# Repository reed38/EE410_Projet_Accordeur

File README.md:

# EE410_Projet_Accordeur

Réalisation d'un accordeur.
Utilisation d'une carte arduino pour l'échantillonage et le traitement des données, réalisation d'un pcb deux couches pour l'intégration du microphone.
2023_2024 S1
Project EE410

### authors:
Maxime Daniau,

Regnault Edgar

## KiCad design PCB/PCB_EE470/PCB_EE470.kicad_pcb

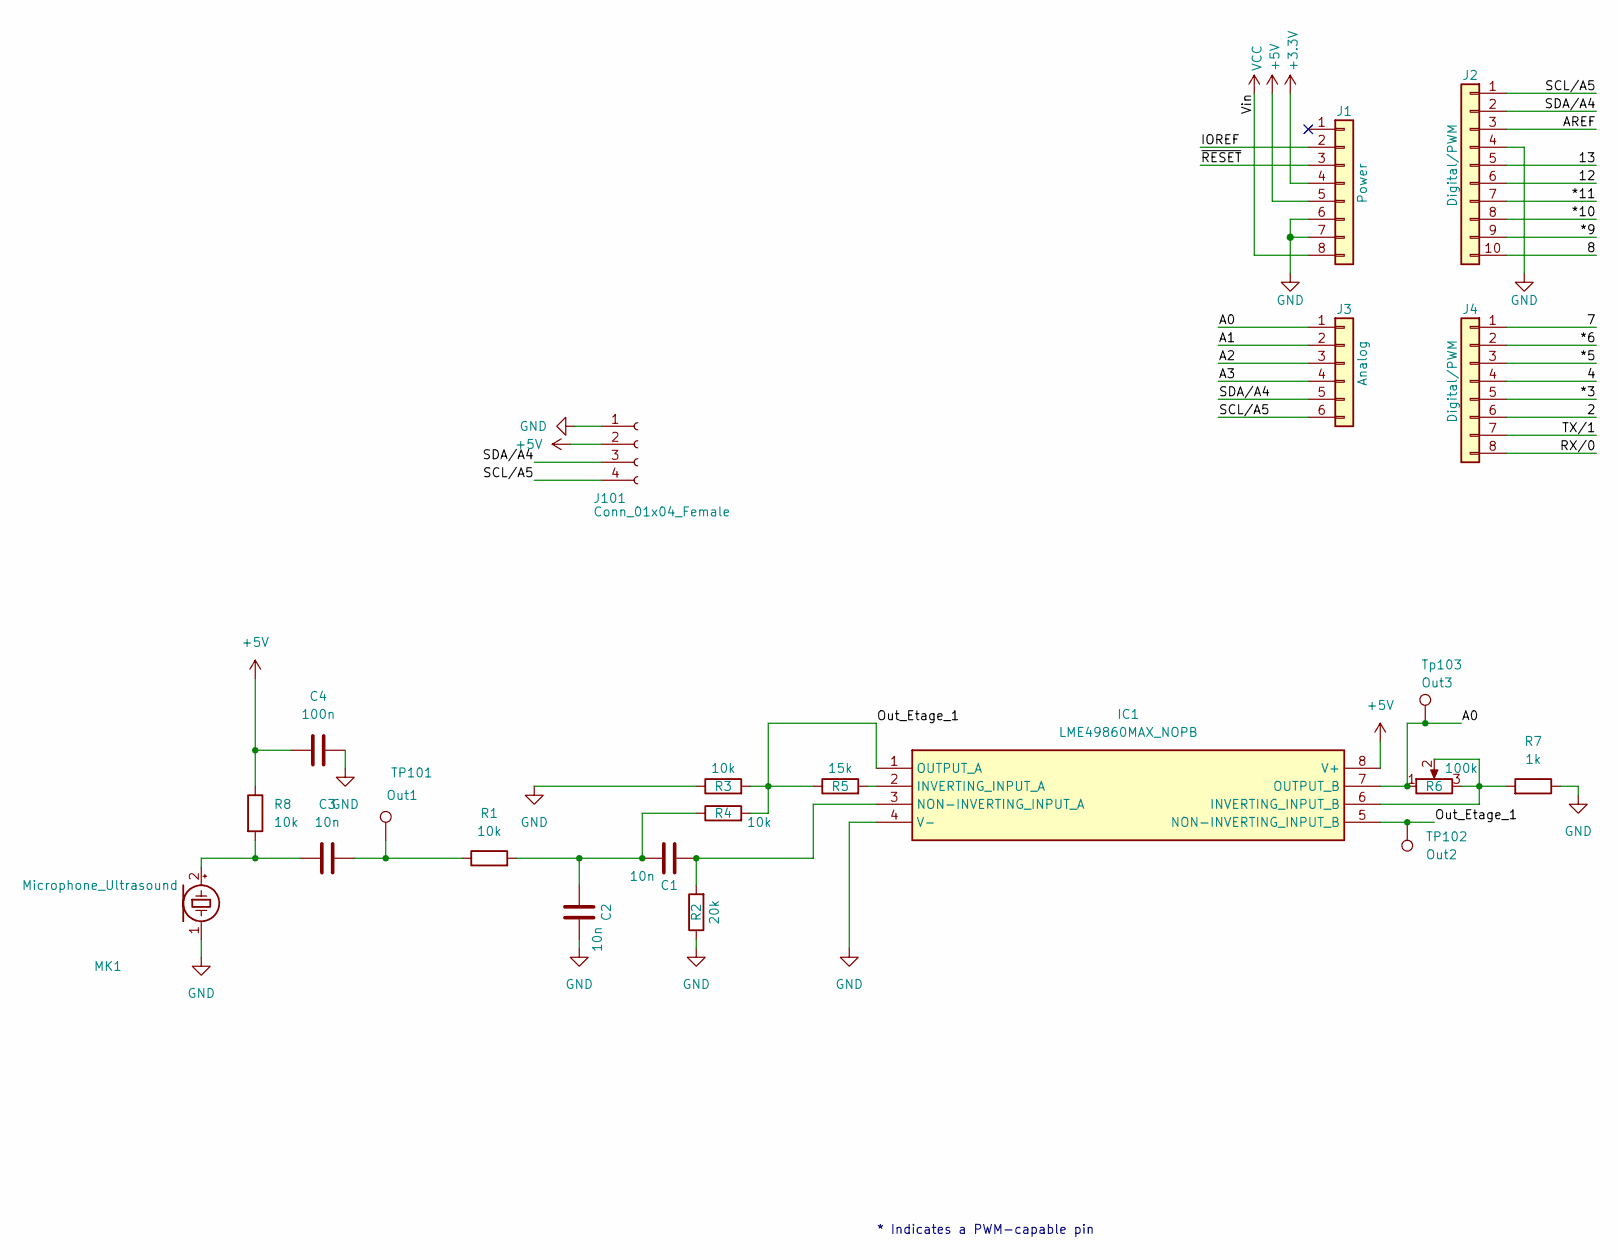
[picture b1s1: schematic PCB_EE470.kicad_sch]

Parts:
C1, C2, C3: 10n; C_1206_3216Metric_Pad1.33x1.80mm_HandSolder
C4: 100n; C_1206_3216Metric_Pad1.33x1.80mm_HandSolder
IC1: LME49860MAX_NOPB; SOIC127P600X175-8N; Mouser Part Number 926-LME49860MAX/NOPB
J1: Power; PinSocket_1x08_P2.54mm_Vertical
J2: Digital/PWM; PinSocket_1x10_P2.54mm_Vertical
J3: Analog; PinSocket_1x06_P2.54mm_Vertical
J4: Digital/PWM; PinSocket_1x08_P2.54mm_Vertical
J101: Conn_01x04_Female; JST_XH_B4B-XH-A_1x04_P2.50mm_Vertical
MK1: Microphone_Ultrasound; D_A-405_P2.54mm_Vertical_AnodeUp
R1, R3, R4, R8: 10k; R_1206_3216Metric_Pad1.30x1.75mm_HandSolder
R2: 20k; R_0805_2012Metric_Pad1.20x1.40mm_HandSolder
R5: 15k; R_0805_2012Metric_Pad1.20x1.40mm_HandSolder
R6: 100k; Potentiometer_Vishay_T73XW_Horizontal
R7: 1k; R_1206_3216Metric_Pad1.30x1.75mm_HandSolder
TP101: Out1; TestPoint_Loop_D3.80mm_Drill2.0mm
TP102: Out2; TestPoint_Loop_D3.80mm_Drill2.0mm
Tp103: Out3; TestPoint_Loop_D3.80mm_Drill2.0mm

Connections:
+3V3: J1.4
+5V: C4.1, IC1.8 (V+), J1.5, J101.2, R8.1
/2: J4.6
/4: J4.4
/7: J4.1
/8: J2.10
/12: J2.6
/13: J2.5
/*3: J4.5
/*5: J4.3
/*6: J4.2
/*9: J2.9
/*10: J2.8
/*11: J2.7
/A0: IC1.7 (OUTPUT_B), J3.1, R6.1, Tp103.1
/A1: J3.2
/A2: J3.3
/A3: J3.4
/AREF: J2.3
/IOREF: J1.2
/Out_Etage_1: IC1.1 (OUTPUT_A), IC1.5 (NON-INVERTING_INPUT_B), R3.2, R4.2, R5.1, TP102.1
/RX/0: J4.8
/SCL/A5: J2.1, J3.6, J101.4
/SDA/A4: J2.2, J3.5, J101.3
/TX/1: J4.7
/~RESET: J1.3
GND: C2.1, C4.2, IC1.4 (V-), J1.6, J1.7, J2.4, J101.1, MK1.1 (-), R2.1, R3.1, R7.1
unnamed: C1.1, C2.2, R1.2, R4.1
unnamed: C3.2, R1.1, TP101.1
unnamed: IC1.2 (INVERTING_INPUT_A), R5.2
unnamed: IC1.6 (INVERTING_INPUT_B), R6.2, R6.3, R7.2
unnamed: C1.2, IC1.3 (NON-INVERTING_INPUT_A), R2.2
unnamed: C3.1, MK1.2 (+), R8.2
VCC: J1.8

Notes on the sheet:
* Indicates a PWM-capable pin

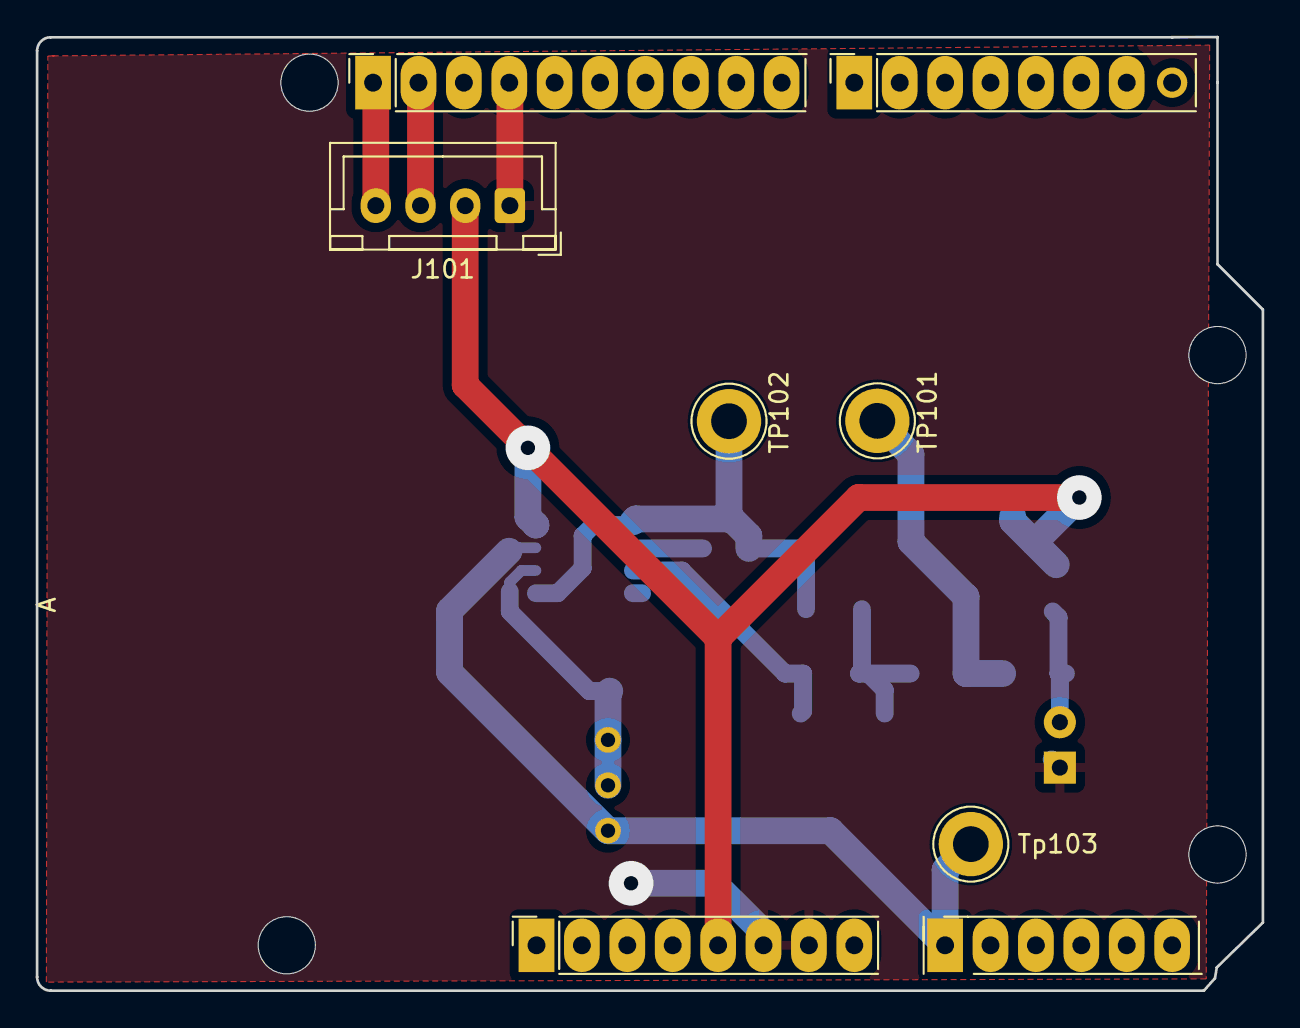
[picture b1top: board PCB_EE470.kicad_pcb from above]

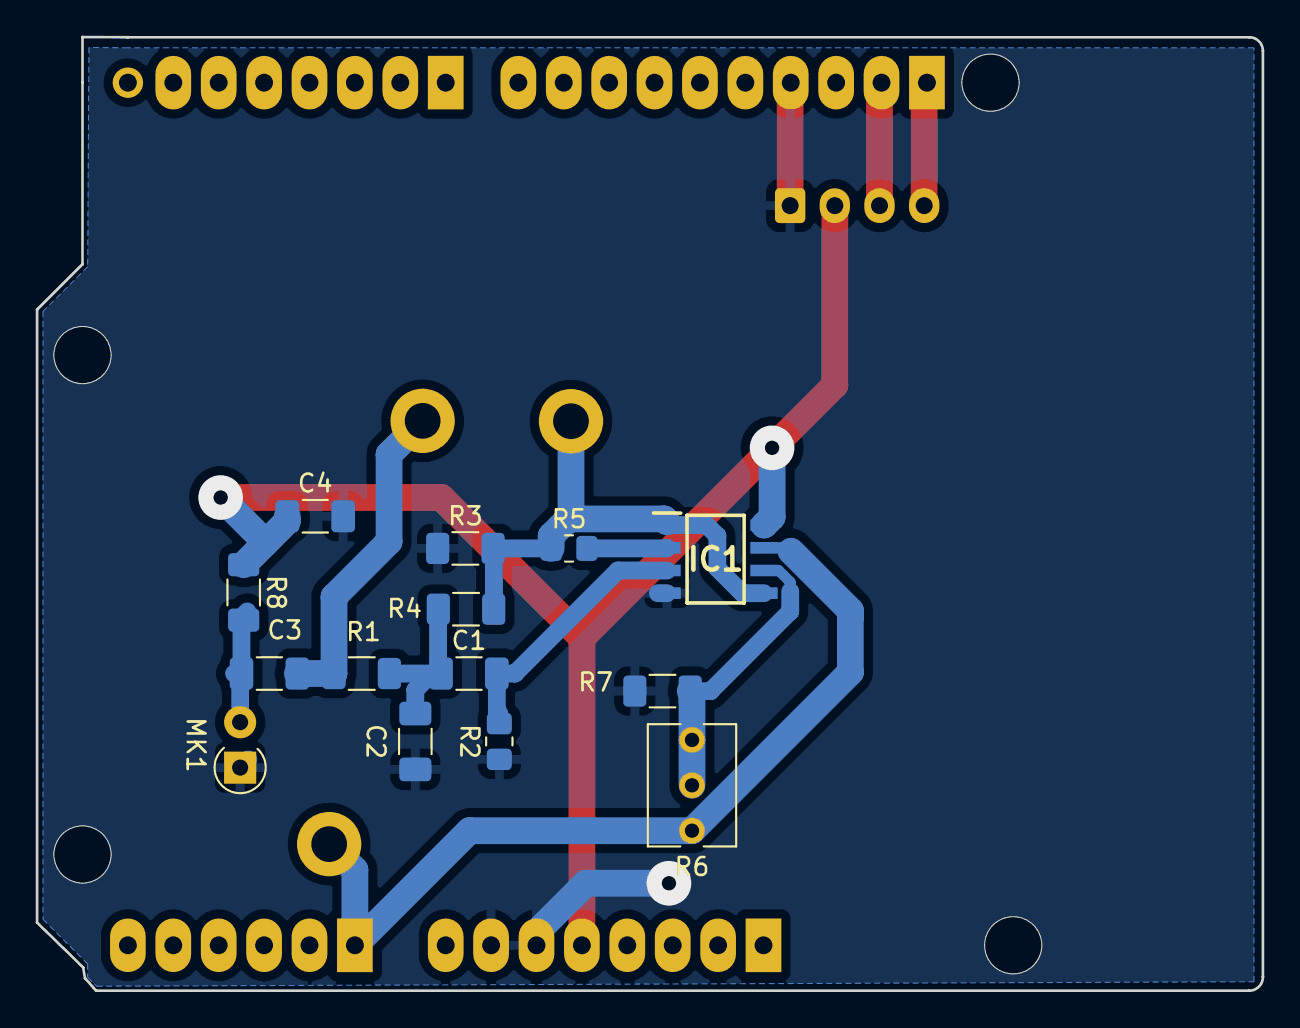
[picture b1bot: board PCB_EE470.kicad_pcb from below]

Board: 2 copper layers, 68.6 x 53.4 mm, 26 parts (14 on the bottom side), 12 nets.

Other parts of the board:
MH1, MH2, MH3, MH4: MountingHole_3.2mm

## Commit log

2023-09-22 création dossiers docs
2023-09-22 rajout doc arduino
2023-09-23 ajout schéma
2023-09-23 ajout readme
2023-09-29 capteur description
    desccription du capteur
2023-09-29 Valeur du capteur
    Description du capteur
2023-09-29 ajout du code de démo
2023-10-06 tableau note de musique
    C'est les fréquences de notes de musique
2023-10-22 ajout de la liste ds composants commandés
2023-11-10 ajout fichiers simu
2023-11-26 ajout salllen key
2023-11-27 pcb et schemataic kicad bien avancés mais c'est 1h30 donc go dormir
2023-11-27 pcb good normalement
2023-11-28 ajout port jst écran arduino
2023-12-05 Create test_afficheur
    test l'afficheur
2023-12-05 test l'afficheur
    test l'afficheur
